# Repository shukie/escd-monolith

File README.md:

# escd-monolith keyboard

The "escd-monolith" keyboard is a single layer aluminum PCB keyboard with 3x12 column staggered keys, 8 thumb keys, and big delete and escape keys (46 keys total).
There are no LEDs, only for CHERRY MX Ultra Low Profile switches and Elite-Pi controller.

It's thin and rigid, but the keys are noisy and it's difficult to print keycaps.
I hope this is helpful in some way, but I don't recommend doing it exactly as is.

"escd" is pronounced as "escaped.”

## Design

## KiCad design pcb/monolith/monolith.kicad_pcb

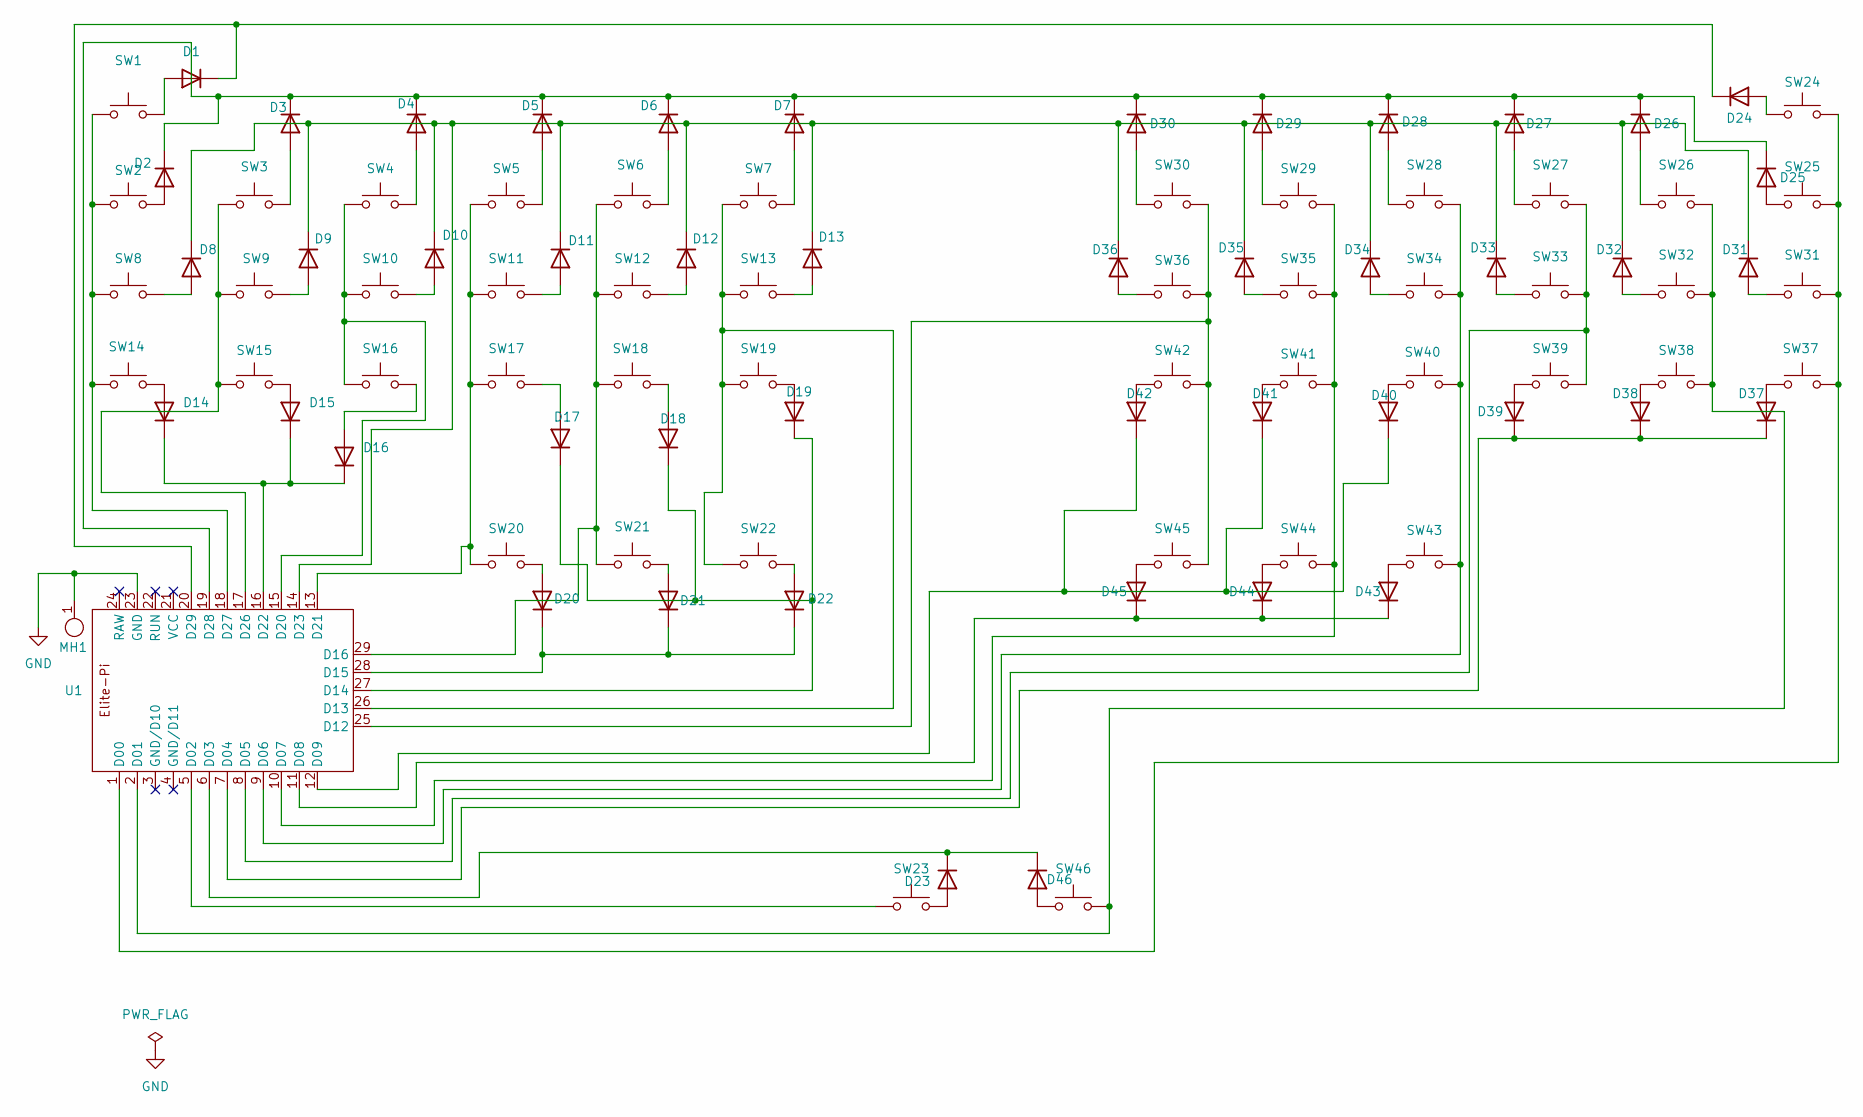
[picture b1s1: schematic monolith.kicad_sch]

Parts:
D1, D2, D3, D4, D5, D6, D7, D8, D9, D10, D11, D12, D13, D14, D15, D16, D17, D18, D19, D20, D21, D22, D23, D24, D25, D26, D27, D28, D29, D30, D31, D32, D33, D34, D35, D36, D37, D38, D39, D40, D41, D42, D43, D44, D45, D46: Diode; 1N4148W
MH1: GroundedMountingHole
SW1, SW23, SW24, SW46: MX-ULP; Cherry-MX-ULP-SMD-wide
SW2, SW3, SW4, SW5, SW6, SW7, SW8, SW9, SW10, SW11, SW12, SW13, SW14, SW15, SW16, SW17, SW18, SW19, SW20, SW21, SW22, SW25, SW26, SW27, SW28, SW29, SW30, SW31, SW32, SW33, SW34, SW35, SW36, SW37, SW38, SW39, SW40, SW41, SW42, SW43, SW44, SW45: MX-ULP; Cherry-MX-ULP-SMD
U1: Elite-Pi; Elite-Pi-SMD

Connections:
GND: MH1.1, U1.23 (GND)
unnamed: D1.2 (A), SW1.2
unnamed: D1.1 (K), D24.1 (K), U1.20 (D29)
unnamed: D2.2 (A), SW2.2
unnamed: D2.1 (K), D3.1 (K), D4.1 (K), D5.1 (K), D6.1 (K), D7.1 (K), D25.1 (K), D26.1 (K), D27.1 (K), D28.1 (K), D29.1 (K), D30.1 (K), U1.19 (D28)
unnamed: D3.2 (A), SW3.2
unnamed: D4.2 (A), SW4.2
unnamed: D5.2 (A), SW5.2
unnamed: D6.2 (A), SW6.2
unnamed: D7.2 (A), SW7.2
unnamed: D8.2 (A), SW8.2
unnamed: D9.2 (A), SW9.2
unnamed: D10.2 (A), SW10.2
unnamed: D8.1 (K), D9.1 (K), D10.1 (K), D11.1 (K), D12.1 (K), D13.1 (K), D31.1 (K), D32.1 (K), D33.1 (K), D34.1 (K), D35.1 (K), D36.1 (K), U1.14 (D23)
unnamed: D11.2 (A), SW11.2
unnamed: D12.2 (A), SW12.2
unnamed: D13.2 (A), SW13.2
unnamed: D14.2 (A), SW14.2
unnamed: D14.1 (K), D15.1 (K), D16.1 (K), U1.16 (D22)
unnamed: D15.2 (A), SW15.2
unnamed: D16.2 (A), SW16.2
unnamed: D17.2 (A), SW17.2
unnamed: D17.1 (K), D18.1 (K), D19.1 (K), U1.27 (D14)
unnamed: D18.2 (A), SW18.2
unnamed: D19.2 (A), SW19.2
unnamed: D20.2 (A), SW20.2
unnamed: D20.1 (K), D21.1 (K), D22.1 (K), U1.28 (D15)
unnamed: D21.2 (A), SW21.2
unnamed: D22.2 (A), SW22.2
unnamed: D23.2 (A), SW23.2
unnamed: D23.1 (K), D46.1 (K), U1.6 (D03)
unnamed: D24.2 (A), SW24.1
unnamed: D25.2 (A), SW25.1
unnamed: D26.2 (A), SW26.1
unnamed: D27.2 (A), SW27.1
unnamed: D28.2 (A), SW28.1
unnamed: D29.2 (A), SW29.1
unnamed: D30.2 (A), SW30.1
unnamed: D31.2 (A), SW31.1
unnamed: D32.2 (A), SW32.1
unnamed: D33.2 (A), SW33.1
unnamed: D34.2 (A), SW34.1
unnamed: D35.2 (A), SW35.1
unnamed: D36.2 (A), SW36.1
unnamed: D37.2 (A), SW37.1
unnamed: D37.1 (K), D38.1 (K), D39.1 (K), U1.7 (D04)
unnamed: D38.2 (A), SW38.1
unnamed: D39.2 (A), SW39.1
unnamed: D40.2 (A), SW40.1
unnamed: D40.1 (K), D41.1 (K), D42.1 (K), U1.12 (D09)
unnamed: D41.2 (A), SW41.1
unnamed: D42.2 (A), SW42.1
unnamed: D43.2 (A), SW43.1
unnamed: D43.1 (K), D44.1 (K), D45.1 (K), U1.11 (D08)
unnamed: D44.2 (A), SW44.1
unnamed: D45.2 (A), SW45.1
unnamed: D46.2 (A), SW46.1
unnamed: SW24.2, SW25.2, SW31.2, SW37.2, U1.1 (D00)
unnamed: SW26.2, SW32.2, SW38.2, SW46.2, U1.2 (D01)
unnamed: SW23.1, U1.5 (D02)
unnamed: SW27.2, SW33.2, SW39.2, U1.8 (D05)
unnamed: SW28.2, SW34.2, SW40.2, SW43.2, U1.9 (D06)
unnamed: SW29.2, SW35.2, SW41.2, SW44.2, U1.10 (D07)
unnamed: SW30.2, SW36.2, SW42.2, SW45.2, U1.25 (D12)
unnamed: SW7.1, SW13.1, SW19.1, SW22.1, U1.26 (D13)
unnamed: SW6.1, SW12.1, SW18.1, SW21.1, U1.29 (D16)
unnamed: SW4.1, SW10.1, SW16.1, U1.15 (D20)
unnamed: SW5.1, SW11.1, SW17.1, SW20.1, U1.13 (D21)
unnamed: SW3.1, SW9.1, SW15.1, U1.17 (D26)
unnamed: SW1.1, SW2.1, SW8.1, SW14.1, U1.18 (D27)

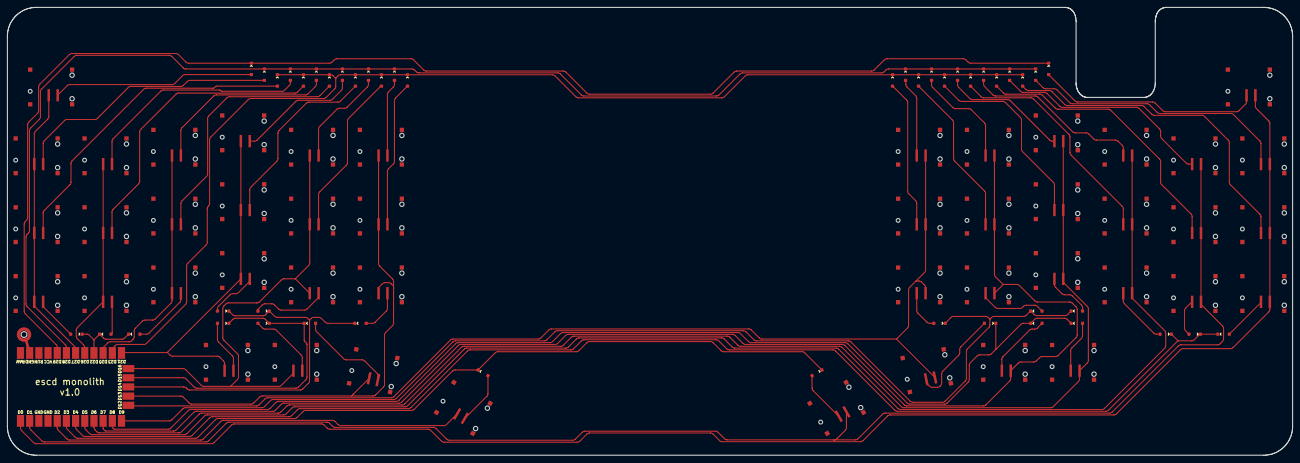
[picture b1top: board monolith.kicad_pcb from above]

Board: 2 copper layers, 355.6 x 123.9 mm, 94 parts (0 on the bottom side), 70 nets.
